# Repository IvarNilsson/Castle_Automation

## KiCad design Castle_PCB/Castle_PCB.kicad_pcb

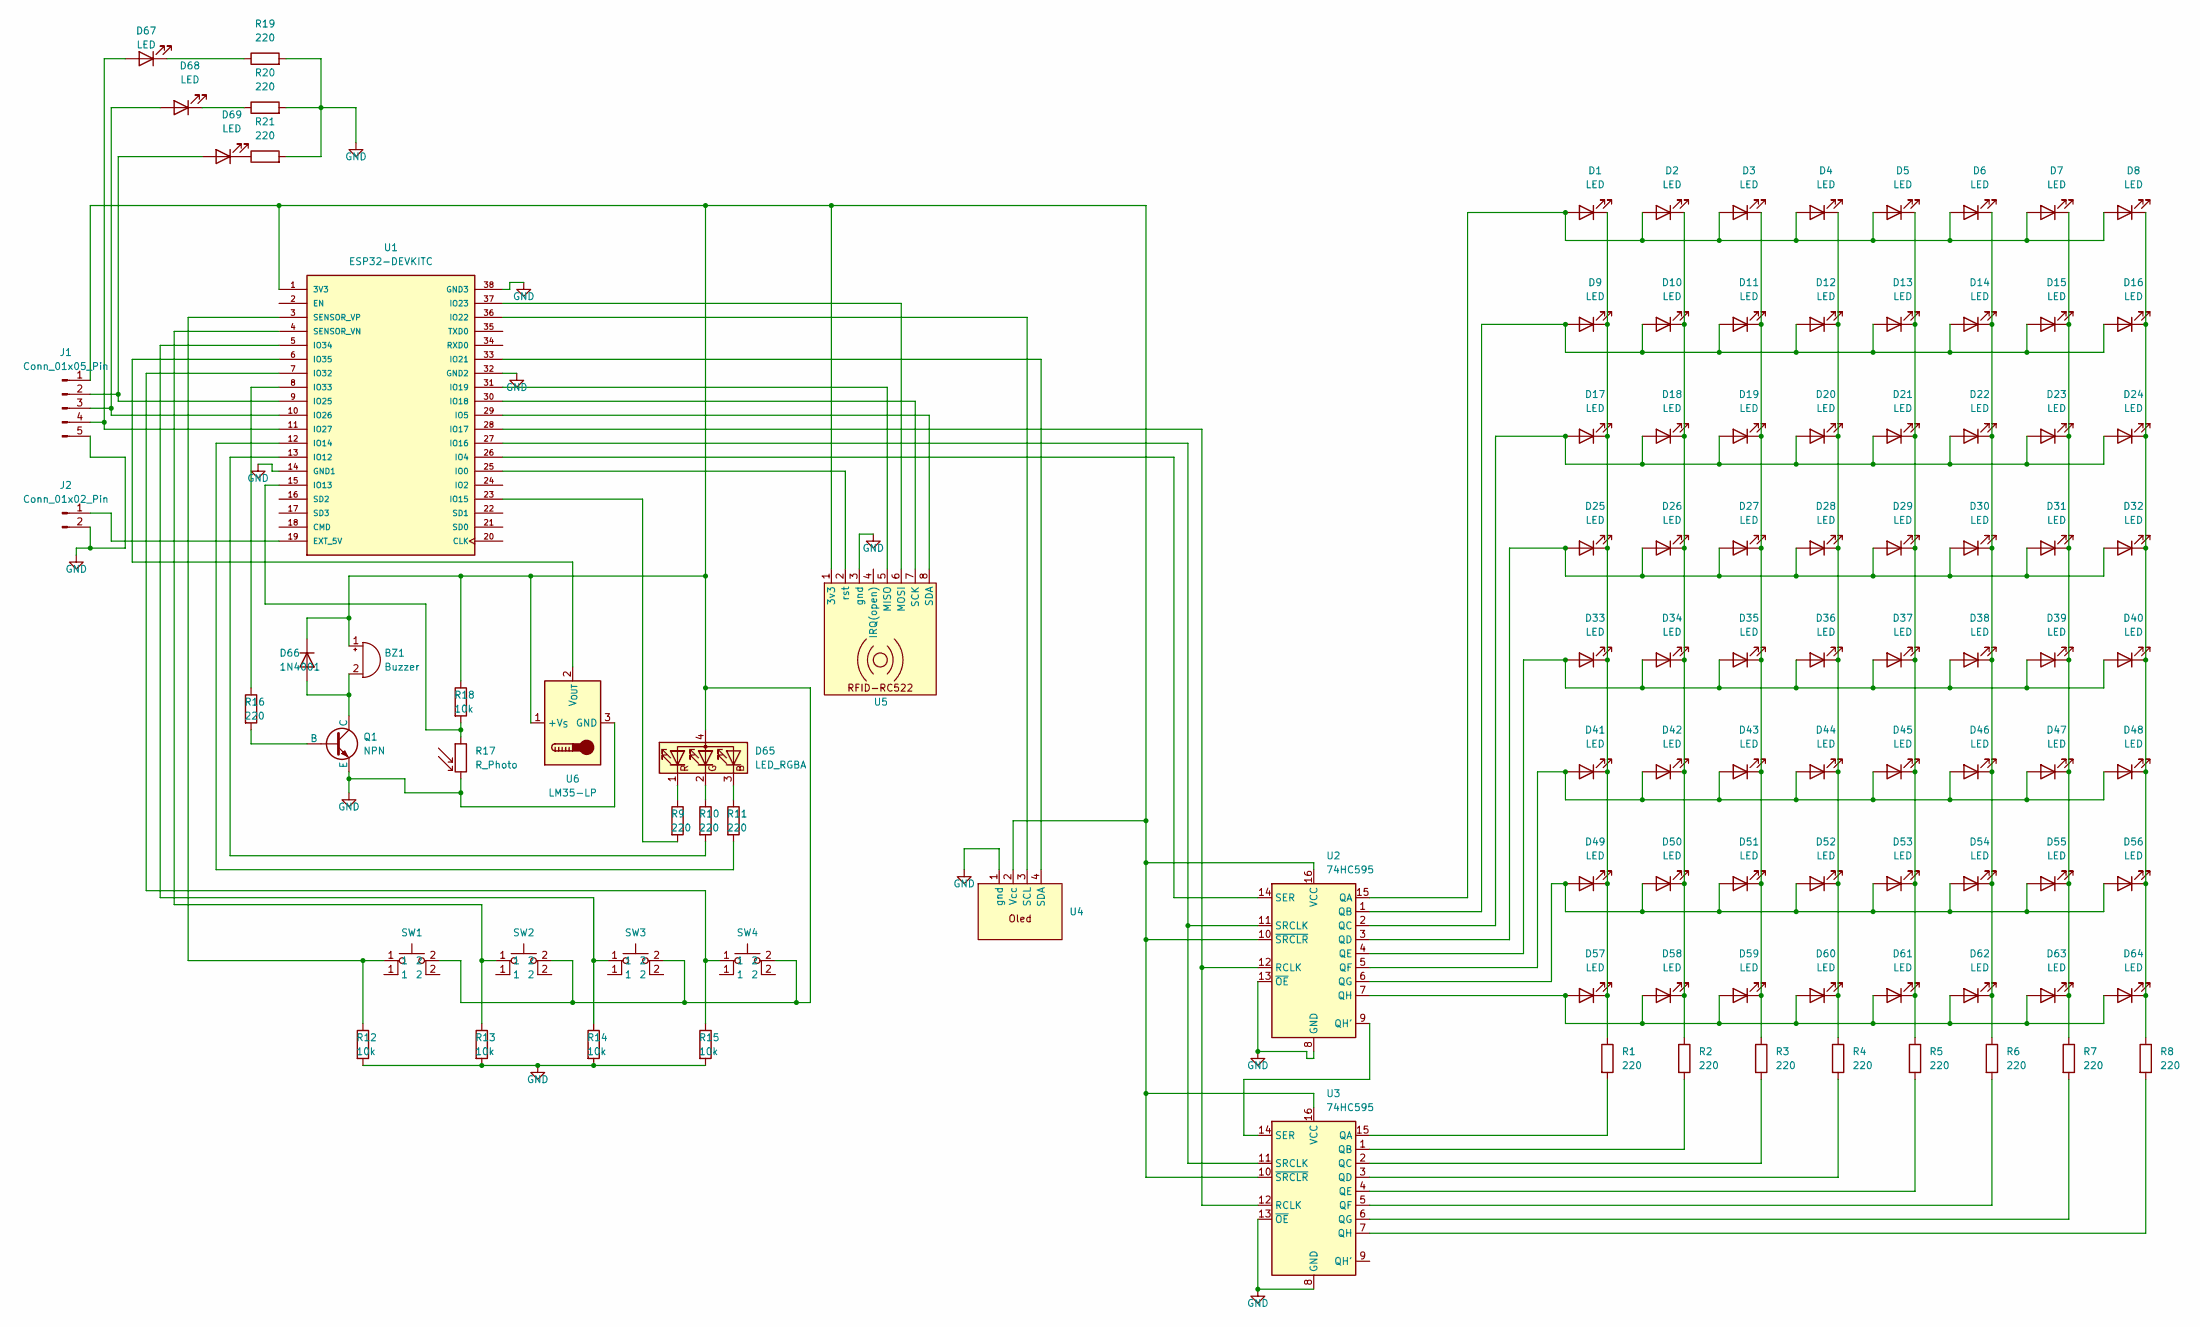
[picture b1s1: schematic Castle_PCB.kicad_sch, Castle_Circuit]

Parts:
BZ1: Buzzer; Buzzer_12x9.5RM7.6
D1, D2, D3, D4, D5, D6, D7, D8, D9, D10, D11, D12, D13, D14, D15, D16, D17, D18, D19, D20, D21, D22, D23, D24, D25, D26, D27, D28, D29, D30, D31, D32, D33, D34, D35, D36, D37, D38, D39, D40, D41, D42, D43, D44, D45, D46, D47, D48, D49, D50, D51, D52, D53, D54, D55, D56, D57, D58, D59, D60, D61, D62, D63, D64, D67, D68, D69: LED; LED_D5.0mm
D65: LED_RGBA; RGB_led_THT
D66: 1N4001; D_DO-41_SOD81_P10.16mm_Horizontal
J1: Conn_01x05_Pin; PinHeader_1x05_P2.54mm_Vertical
J2: Conn_01x02_Pin; PinHeader_1x02_P2.54mm_Vertical
Q1: NPN; TO-92L_Inline
R1, R2, R3, R4, R5, R6, R7, R8, R9, R10, R11, R16, R19, R20, R21: 220; R_Axial_DIN0207_L6.3mm_D2.5mm_P7.62mm_Horizontal
R12, R13, R14, R15, R18: 10k; R_Axial_DIN0207_L6.3mm_D2.5mm_P7.62mm_Horizontal
R17: R_Photo; PhotoResistor
SW1, SW2, SW3, SW4: SW_PUSH-12mm
U1: ESP32-DEVKITC; MODULE_ESP32-DEVKITC; PARTREV N/A
U2, U3: 74HC595; DIP-16_W7.62mm_LongPads
U4: oled_0.96
U5: RFID-RC522
U6: LM35-LP; TO-92_Inline

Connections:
GND: J1.5, J2.2, Q1.3 (E), R12.2, R13.2, R14.2, R15.2, R17.2, R19.2, R20.2, R21.2, U1.14 (GND1), U1.32 (GND2), U1.38 (GND3), U2.8 (GND), U2.13 (~OE), U3.8 (GND), U3.13 (~OE), U4.1 (gnd), U5.3 (gnd), U6.3 (GND)
unnamed: BZ1.2 (+), D66.2 (A), Q1.1 (C)
unnamed: BZ1.1 (-), D65.4 (A), D66.1 (K), J1.1, R18.1, SW1.2, SW2.2, SW3.2, SW4.2, U1.1 (3V3), U2.10 (~SRCLR), U2.16 (VCC), U3.10 (~SRCLR), U3.16 (VCC), U4.2 (Vcc), U5.1 (3v3), U6.1 (+V_{S})
unnamed: D1.2 (A), D2.2 (A), D3.2 (A), D4.2 (A), D5.2 (A), D6.2 (A), D7.2 (A), D8.2 (A), U2.15 (QA)
unnamed: D1.1 (K), D9.1 (K), D17.1 (K), D25.1 (K), D33.1 (K), D41.1 (K), D49.1 (K), D57.1 (K), R1.1
unnamed: D9.2 (A), D10.2 (A), D11.2 (A), D12.2 (A), D13.2 (A), D14.2 (A), D15.2 (A), D16.2 (A), U2.1 (QB)
unnamed: D2.1 (K), D10.1 (K), D18.1 (K), D26.1 (K), D34.1 (K), D42.1 (K), D50.1 (K), D58.1 (K), R2.1
unnamed: D3.1 (K), D11.1 (K), D19.1 (K), D27.1 (K), D35.1 (K), D43.1 (K), D51.1 (K), D59.1 (K), R3.1
unnamed: D4.1 (K), D12.1 (K), D20.1 (K), D28.1 (K), D36.1 (K), D44.1 (K), D52.1 (K), D60.1 (K), R4.1
unnamed: D5.1 (K), D13.1 (K), D21.1 (K), D29.1 (K), D37.1 (K), D45.1 (K), D53.1 (K), D61.1 (K), R5.1
unnamed: D6.1 (K), D14.1 (K), D22.1 (K), D30.1 (K), D38.1 (K), D46.1 (K), D54.1 (K), D62.1 (K), R6.1
unnamed: D7.1 (K), D15.1 (K), D23.1 (K), D31.1 (K), D39.1 (K), D47.1 (K), D55.1 (K), D63.1 (K), R7.1
unnamed: D8.1 (K), D16.1 (K), D24.1 (K), D32.1 (K), D40.1 (K), D48.1 (K), D56.1 (K), D64.1 (K), R8.1
unnamed: D17.2 (A), D18.2 (A), D19.2 (A), D20.2 (A), D21.2 (A), D22.2 (A), D23.2 (A), D24.2 (A), U2.2 (QC)
unnamed: D25.2 (A), D26.2 (A), D27.2 (A), D28.2 (A), D29.2 (A), D30.2 (A), D31.2 (A), D32.2 (A), U2.3 (QD)
unnamed: D33.2 (A), D34.2 (A), D35.2 (A), D36.2 (A), D37.2 (A), D38.2 (A), D39.2 (A), D40.2 (A), U2.4 (QE)
unnamed: D41.2 (A), D42.2 (A), D43.2 (A), D44.2 (A), D45.2 (A), D46.2 (A), D47.2 (A), D48.2 (A), U2.5 (QF)
unnamed: D49.2 (A), D50.2 (A), D51.2 (A), D52.2 (A), D53.2 (A), D54.2 (A), D55.2 (A), D56.2 (A), U2.6 (QG)
unnamed: D57.2 (A), D58.2 (A), D59.2 (A), D60.2 (A), D61.2 (A), D62.2 (A), D63.2 (A), D64.2 (A), U2.7 (QH)
unnamed: D65.3 (BK), R11.1
unnamed: D65.2 (GK), R10.1
unnamed: D65.1 (RK), R9.1
unnamed: D67.2 (A), J1.4, U1.11 (IO27)
unnamed: D67.1 (K), R19.1
unnamed: D68.2 (A), J1.3, U1.10 (IO26)
unnamed: D68.1 (K), R20.1
unnamed: D69.2 (A), J1.2, U1.9 (IO25)
unnamed: D69.1 (K), R21.1
unnamed: J2.1, U1.19 (EXT_5V)
unnamed: Q1.2 (B), R16.2
unnamed: U1.25 (IO0), U5.2 (rst)
unnamed: U1.26 (IO4), U2.14 (SER)
unnamed: U1.29 (IO5), U5.8 (SDA)
unnamed: R10.2, U1.13 (IO12)
unnamed: R17.1, R18.2, U1.15 (IO13)
unnamed: R11.2, U1.12 (IO14)
unnamed: R9.2, U1.23 (IO15)
unnamed: U1.27 (IO16), U2.11 (SRCLK), U3.11 (SRCLK)
unnamed: U1.28 (IO17), U2.12 (RCLK), U3.12 (RCLK)
unnamed: U1.30 (IO18), U5.7 (SCK)
unnamed: U1.31 (IO19), U5.5 (MISO)
unnamed: U1.33 (IO21), U4.4 (SDA)
unnamed: U1.36 (IO22), U4.3 (SCL)
unnamed: U1.37 (IO23), U5.6 (MOSI)
unnamed: R15.1, SW4.1, U1.7 (IO32)
unnamed: R16.1, U1.8 (IO33)
unnamed: R14.1, SW3.1, U1.5 (IO34)
unnamed: U1.6 (IO35), U6.2 (V_{OUT})
unnamed: R13.1, SW2.1, U1.4 (SENSOR_VN)
unnamed: R12.1, SW1.1, U1.3 (SENSOR_VP)
unnamed: U2.9 (QH'), U3.14 (SER)
unnamed: R1.2, U3.15 (QA)
unnamed: R2.2, U3.1 (QB)
unnamed: R3.2, U3.2 (QC)
unnamed: R4.2, U3.3 (QD)
unnamed: R5.2, U3.4 (QE)
unnamed: R6.2, U3.5 (QF)
unnamed: R7.2, U3.6 (QG)
unnamed: R8.2, U3.7 (QH)

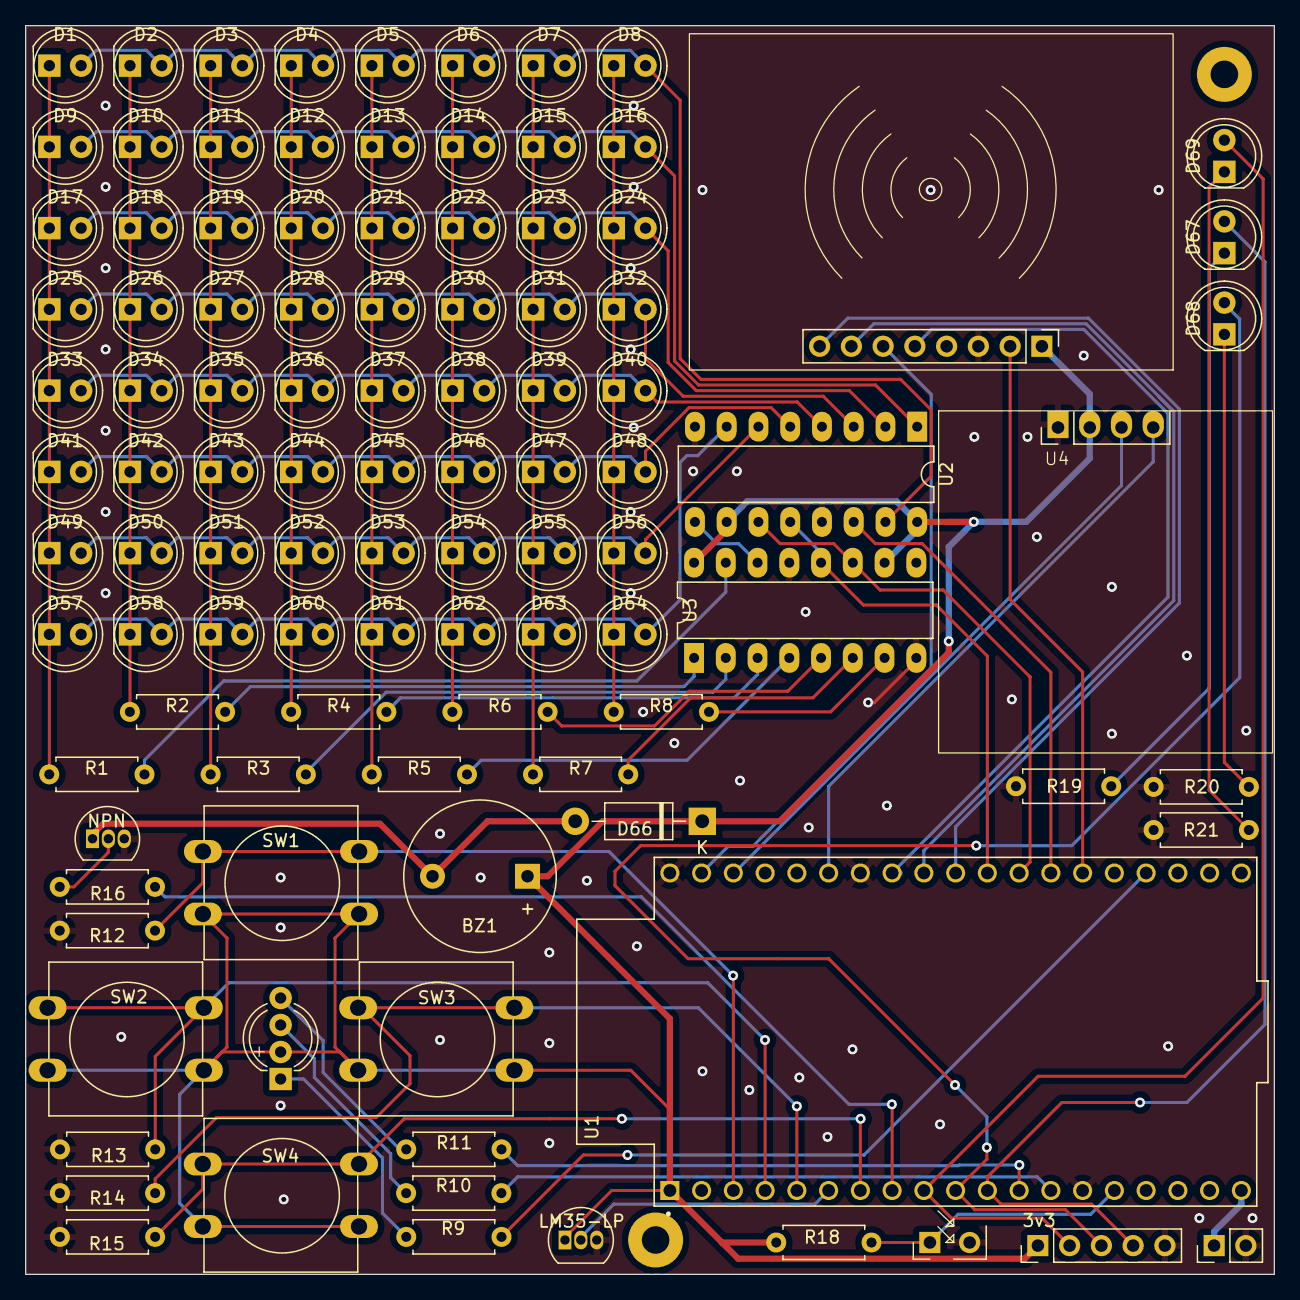
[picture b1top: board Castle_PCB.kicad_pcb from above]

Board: 2 copper layers, 99.9 x 99.9 mm, 104 parts (0 on the bottom side), 59 nets.

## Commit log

2022-11-04 included main
2022-11-04 added a circuit_diagram
2022-11-04 changed circuit_diagram to png
2022-11-04 Create LICENSE
2023-09-12 back at it! Almost done with PCB
2023-09-24 pcb done!
2023-09-24 fixed some nice scripts using arduino-cli wokrs well on ubunto
2023-09-24 try to fix git
2023-09-24 Finally fixed error squigels for simple esp32 code
2023-09-24 works ok but still some buggs with PCB
2023-09-24 Matrix clock was to fast so now it works
2023-09-25 more tests
2023-10-14 fun small tdc program
2023-11-18 Started work on new PCB
2023-11-22 Script fixes and more
2023-11-23 First RTOS test
2023-11-24 now syntax and imports of libs finaly :-/
2023-11-24 progress
2023-11-28 small fix
2023-11-28 script improvmnets
2023-11-28 fixed ivar_lib
2023-12-02 some progress but not finished with the matrix :/
2023-12-03 daily progress
2024-01-04 new solder iron and now more of the circuit is solderd :), todo: fix RTOS matrix us delay and RFID
2024-01-06 everything exept one green led works now its time to RTOS it all ;)
2024-01-11 RFID module and all leds working :)
2024-02-16 new tdc :)
2024-02-16 libraries
